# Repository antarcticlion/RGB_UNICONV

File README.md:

# RGB_UNICONV  

PCBs for Retro computer display connector convertion.  

---
  
## available configulations  
- Digital RGB DIN8p PC-8001 type pinout to DE15 VGA pinout (support ex. PC-8001/8801/9801/FM-7/MZ-700/Basic master level3/Pasopia PA7010/X1 turbo model 40)  
- Analog RGB DSUB15p 2row(DA15) PC-8801mk2SR type pinout to DE15 VGA pinout (support ex. PC-8801SR～/9801U･VM～/X68000)  
- Digital RGB DIN6p X1/X1turbo(without model 40) type pinout to DE15 VGA pinout  
- Analog RGB DSUB9p (DE9) PC-98XA/XL/XL2/RL type pinout to DE15 VGA pinout
- Digital RGB DSUB9p (DE9) FM77 type pinout to DE15 VGA pinout  (support FM77-D1/D2/L4/L2/AV)

---  
  
## news  

2022/09/27 Added PC98 Hi-resolution model (XA/XL/XL2/RL) DE9 configulation  
2022/09/27 Added FM77 Digital RGB 8 colors (D1/D2/L2/L4(8color only)/AV) DE9 configulation  

2022/07/30 Each PCB: Added "Licensed under CERN-OHL-W v2" somewhere on the silkscreen.

2022/07/20 Added X1/X1turbo DIN6 configulation  
2022/07/20 Added PC8801SR etc. DA15 configulation  
  
2022/07/09 Added pin type DE15 out PCB  
  
2022/06/25 Added the assembly procedure to the wiki. Since it is written in Japanese, please machine-translate it into your native language.  
https://github.com/antarcticlion/RGB_UNICONV/wiki/How-to-make  

---
## photos  

---

## GERBERs and BOMs

---  

### Digital RGB DIN8p PC-8001 type pinout to DE15 VGA pinout (support ex. PC-8001/8801/9801/FM-7/MZ-700/Pasopia PA7010/Basic master level3/X1 turbo model 40)  
  Received a report on the operation of the PC6001Mk2 (8 colors), and SMC777 (digital RGB).  
  
  #### lastest gerber 
  ##### DIN8_PC8001_IN PCB  
　　　https://github.com/antarcticlion/RGB_UNICONV/raw/main/DIN8_PC8001_IN/gerber/RGB_CONN_CHG_DIN8_ST4A.zip  
　　　PC-8001 type pin-out RGB display 8-pin DIN connector Breakout board.  
　　　Adjust the level using a 150Ω resistor.  

  ##### ANGLE_CHANGE_MID PCB 
　　　https://github.com/antarcticlion/RGB_UNICONV/blob/main/ANGLE_CHANGE_MID/gerber/RGB_CONN_CHG_MID_ST3A.zip  
　　　By sandwiching this board between the input board and the output board, the position of the signal pin is changed by 90 degrees.  
　　　Used when the connector interferes.  
　　　You can also combine two boards to extend the overall length.  
　　　When using two board for extension, make sure that the direction and orientation are the same.  
　　　Doing so will cause the signal to return to its original position.  

  ##### DE15_OUT PCB  
　　　https://github.com/antarcticlion/RGB_UNICONV/raw/main/DE15_OUT/gerber/RGB_CONN_CHG_DE15_CUP_ST2A.zip  
　　　Breakout board for solder cup type D-sub 15-pin 3-rows (DE15) connector.  
  
　　　https://github.com/antarcticlion/RGB_UNICONV/raw/main/DE15_OUT/gerber/RGB_CONN_CHG_DE15_ST1A.zip  
　　　Breakout board for pin type D-sub 15-pin 3-rows (DE15) connector.  

#### BOM (short profile)  
 - DIN8_PC8001_IN PCB x1  
 - DE15_OUT PCB x1  
 - 150ohm register x3  
 - DE15 female connector (solder cup) x1  
 - PCB mount din8 connector x1  
 - long pin header(minimum height 6mm) 3p x2  
  
#### BOM (90° angle profile)  
 - DIN8_PC8001_IN PCB x1  
 - ANGLE_CHANGE_MID PCB x1  
 - DE15_OUT PCB x1  
 - 150ohm register x3  
 - DE15 female connector (solder cup) x1  
 - PCB mount din8 connector x1  
 - long pin header(minimum height 6mm) 3p x4  
  
#### BOM (long profile)  
 - DIN8_PC8001_IN PCB x1  
 - ANGLE_CHANGE_MID PCB x2  
 - DE15_OUT PCB x1  
 - 150ohm register x3  
 - DE15 female connector (solder cup) x1  
 - PCB mount din8 connector x1  
 - long pin header(minimum height 6mm) 3p x6  

---  

### Analog RGB DSUB15p 2row(DA15) PC-8801mk2SR type pinout to DE15 VGA pinout (support ex. PC-8801SR～/9801U･VM～/X68000)  

#### lastest gerber 
##### DA15_PC88SR_IN PCB  
  https://github.com/antarcticlion/RGB_UNICONV/raw/main/DA15_88SR_IN/gerber/RGB_CONN_CHG_DA15_PC88SR_ST2A.zip  

PC-8801mk2SR type pin-out RGB display D-Sub 15pin 2row connector(Solder cup type) Breakout board.
CSYNC and Audio L R are pulled out in the optional pinout.
Confirmed that the CSYNC signal is output by 88SR generations.  and by XL, VX, DX, DA, FA on PC98. It has appeared in major models up to FA, but it seems that it has not appeared since then.
GS / 9821S is unknown.
It seems that PC286 / 386/486 is not available in later models. Probably not all models of X68000 are out.

Audio L R can be expected to output on all models of PC88SR or later / X68000. In PC98, it seems that it is output in the model equipped with FM sound source on the motherboard (confirmed with 98DA)  
On the YM2203-equipped machine, the same sound is produced for both LR.  

##### CSYNC_ANGLE_CHANGE_MID PCB  
https://github.com/antarcticlion/RGB_UNICONV/raw/main/ANGLE_CHANGE_MID/gerber/RGB_CONN_CHG_MID_ST3A.zip  

This angle-change-PCB have prepared a jumper so that you can select the relay of CSYNC and HSYNC that are pulled out as an option.  
This makes it possible to directly connect a PC-8801mk2SR, etc. to the GBS8200 / 8220 / HD-VC9900.  

#### BOM (short profile)  
 - DA15_PC88SR_IN PCB x1  
 - DE15_OUT PCB x1  
 - DA15 male connector (solder cup) x1  
 - DE15 female connector (solder cup) x1  
 - long pin header(minimum height 6mm) 3p x2  
  
#### BOM (90° angle profile)  
 - DA15_PC88SR_IN PCB x1  
 - ANGLE_CHANGE_MID PCB x1  
 - DE15_OUT PCB x1  
 - DA15 male connector (solder cup) x1  
 - DE15 female connector (solder cup) x1  
 - long pin header(minimum height 6mm) 3p x4  
  
#### BOM (long profile)  
 - DA15_PC88SR_IN PCB x1  
 - ANGLE_CHANGE_MID PCB x2  
 - DE15_OUT PCB x1  
 - DA15 male connector (solder cup) x1  
 - DE15 female connector (solder cup) x1  
 - long pin header(minimum height 6mm) 3p x6  

#### BOM (90° angle profile with csync)  
 - DA15_PC88SR_IN PCB x1  
 - CSYNC_ANGLE_CHANGE_MID PCB x1  
 - DE15_OUT PCB x1  
 - DA15 male connector (solder cup) x1  
 - DE15 female connector (solder cup) x1  
 - long pin header(minimum height 6mm) 3p x3  
 - long pin header(minimum height 6mm) 4p x1  
  
#### BOM (long profile with csync)  
 - DA15_PC88SR_IN PCB x1  
 - CSYNC_ANGLE_CHANGE_MID PCB x1  
 - ANGLE_CHANGE_MID PCB x1  
 - DE15_OUT PCB x1  
 - DA15 male connector (solder cup) x1  
 - DE15 female connector (solder cup) x1  
 - long pin header(minimum height 6mm) 3p x5  
 - long pin header(minimum height 6mm) 4p x1  

---

### Digital RGB DIN6p X1/X1turbo(without model 40) type pinout to DE15 VGA pinout  
  
  #### lastest gerber 
  ##### DIN6_X1_IN PCB  
　　　https://github.com/antarcticlion/RGB_UNICONV/raw/main/DIN6_X1_IN/gerber/RGB_CONN_CHG_DIN6_ST4A.zip  
　　　X1/X1turbo type pin-out RGB display 6-pin DIN connector Breakout board.  
　　　Adjust the level using a 150Ω resistor.  

#### BOM (short profile)  
 - DIN6_X1_IN PCB x1  
 - DE15_OUT PCB x1  
 - 150ohm register x3  
 - DE15 female connector (solder cup) x1  
 - PCB mount din8 connector x1  
 - long pin header(minimum height 6mm) 3p x2  
  
#### BOM (90° angle profile)  
 - DIN6_X1_IN PCB x1  
 - ANGLE_CHANGE_MID PCB x1  
 - DE15_OUT PCB x1  
 - 150ohm register x3  
 - DE15 female connector (solder cup) x1  
 - PCB mount din8 connector x1  
 - long pin header(minimum height 6mm) 3p x4  
  
#### BOM (long profile)  
 - DIN6_X1_IN PCB x1  
 - ANGLE_CHANGE_MID PCB x2  
 - DE15_OUT PCB x1  
 - 150ohm register x3  
 - DE15 female connector (solder cup) x1  
 - PCB mount din8 connector x1  
 - long pin header(minimum height 6mm) 3p x6  

---

### Analog RGB DSUB9p (DE9) PC-98XA/XL/XL2/RL type pinout to DE15 VGA pinout  
  
  #### lastest gerber  
  ##### DE9_PC98XL_IN PCB  
　　　https://github.com/antarcticlion/RGB_UNICONV/raw/main/DE9_PC98XL_IN/gerber/RGB_CONN_CHG_DE9_98XL_ST2A.zip  
　　　PC-98XA/XL/XL2/RL type pinout RGB display DSUB 9p (DE9) connector Breakout board.  

#### BOM (short profile)  
 - DE9_PC98XL_IN PCB x1  
 - DE15_OUT PCB x1  
 - DE15 female connector (solder cup) x1  
 - DE9 male connector (solder cup) x1  
 - long pin header(minimum height 6mm) 3p x2  
  
#### BOM (90° angle profile)  
 - DE9_PC98XL_IN PCB x1  
 - ANGLE_CHANGE_MID PCB x1  
 - DE15_OUT PCB x1  
 - DE15 female connector (solder cup) x1  
 - DE9 male connector (solder cup) x1  
 - long pin header(minimum height 6mm) 3p x4  
  
#### BOM (long profile)  
 - DE9_PC98XL_IN PCB x1  
 - ANGLE_CHANGE_MID PCB x2  
 - DE15_OUT PCB x1  
 - DE15 female connector (solder cup) x1  
 - DE9 male connector (solder cup) x1  
 - long pin header(minimum height 6mm) 3p x6  

---

### Digital RGB DSUB9p (DE9) FM77 type pinout to DE15 VGA pinout  (support FM77-D1/D2/L4/L2/AV)
  
  #### lastest gerber 
  ##### DE9_FM77_IN PCB  
　　　https://github.com/antarcticlion/RGB_UNICONV/raw/main/DE9_FM77_IN/gerber/RGB_CONN_CHG_DE9_FM77_ST2A.zip  
　　　FM77 type pinout RGB display DSUB 9p (DE9) connector Breakout board.  
　　　Adjust the level using a 150Ω resistor.  

  ##### ANGLE_CHANGE_DIGITAL_MID PCB
　　　https://github.com/antarcticlion/RGB_UNICONV/raw/main/ANGLE_CHANGE_DIGITAL_MID/gerber/RGB_CONN_CHG_MID_DIGITAL_ST1A.zip  
　　　Digital RGB signal level control angle change board  

#### BOM (short profile)  
  N/A  
  
#### BOM (90° angle profile)  
 - DE9_FM77_IN PCB x1  
 - ANGLE_CHANGE_DIGITAL_MID PCB x1  
 - DE15_OUT PCB x1  
 - 150ohm register x3  
 - DE15 female connector (solder cup) x1  
 - DE9 male connector (solder cup) x1  
 - long pin header(minimum height 6mm) 3p x4  
  
#### BOM (long profile)  
 - DE9_FM77_IN PCB x1  
 - ANGLE_CHANGE_DIGITAL_MID PCB x2  
 - ANGLE_CHANGE_MID PCB x1  
 - DE15_OUT PCB x1  
 - 150ohm register x3  
 - DE15 female connector (solder cup) x1  
 - DE9 male connector (solder cup) x1  
 - long pin header(minimum height 6mm) 3p x6  

---
#  Source of reference
 - PC-8001 type DIN8 RGB Display connector pinout : 改訂2版 PC-9800シリーズ テクニカルデータブック HARDWAER編 ISBN4-7561-1008-8
 - VGA DE15 RGB Display connector pinout : SECOND EDITION THE PROGRAMMER'S PC SOURCEBOOK ISBN1-55615-321-X
 - X1センター -> インターフェイスコネクタ : http://www.x1center.org/
 - Retro PC Gallery (by はせりん) -> 番外編７：FM-8/7/77/77AVシリーズの微妙な非互換性 : http://haserin09.la.coocan.jp/
---

# LICENSE

Copyright Antarcticlion 2022.
This source describes Open Hardware and is licensed under the CERN-OHLW v2

You may redistribute and modify this documentation and make products using it under the terms of the CERN-OHL-W v2 (https:/cern.ch/cern-ohl).
This documentation is distributed WITHOUT ANY EXPRESS OR IMPLIED WARRANTY, INCLUDING OF MERCHANTABILITY, SATISFACTORY QUALITY AND FITNESS FOR A PARTICULAR PURPOSE. Please see the CERN-OHL-W v2 for applicable conditions.
Source location: https://github.com/antarcticlion/RGB_UNICONV
As per CERN-OHL-W v2 section 4.1, should You produce hardware based on these sources, You must maintain the Source Location visible on the external case of the White Rabbit switch or other product you make using this documentation.

 CERN Open Hardware Licence Version 2 - Weakly Reciprocal
- https://spdx.org/licenses/CERN-OHL-W-2.0.html  
- https://github.com/antarcticlion/RGB_UNICONV/raw/main/cern_ohl_w_v2.pdf PDF  
- https://github.com/antarcticlion/RGB_UNICONV/raw/main/cern_ohl_w_v2_howto.pdf PDF

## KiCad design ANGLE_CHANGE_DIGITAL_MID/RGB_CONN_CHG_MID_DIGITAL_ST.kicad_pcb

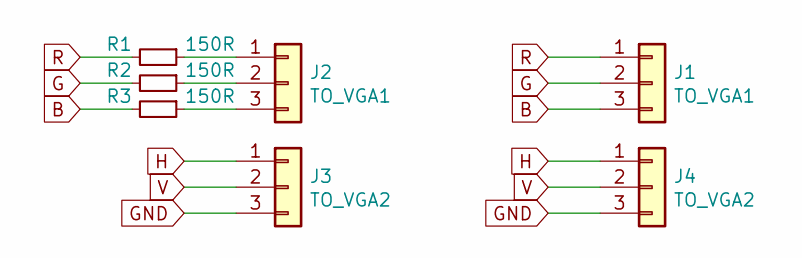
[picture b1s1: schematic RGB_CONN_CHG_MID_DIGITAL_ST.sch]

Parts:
J1, J2: TO_VGA1; PinHeader_1x03_P2.54mm_Vertical
J3, J4: TO_VGA2; PinHeader_1x03_P2.54mm_Vertical
R1, R2, R3: 150R; R_Axial_DIN0204_L3.6mm_D1.6mm_P5.08mm_Horizontal

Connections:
B: J1.3, R3.2
G: J1.2, R2.2
GND: J3.3, J4.3
H: J3.1, J4.1
unnamed: J2.1, R1.1
unnamed: J2.2, R2.1
unnamed: J2.3, R3.1
R: J1.1, R1.2
V: J3.2, J4.2

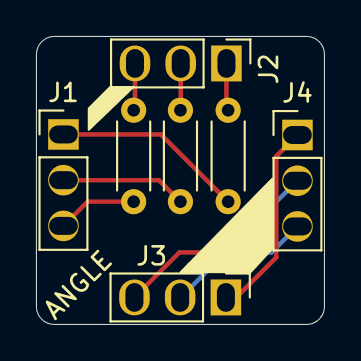
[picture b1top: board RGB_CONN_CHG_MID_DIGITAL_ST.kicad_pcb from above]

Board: 2 copper layers, 16.0 x 16.0 mm, 7 parts (0 on the bottom side), 9 nets.

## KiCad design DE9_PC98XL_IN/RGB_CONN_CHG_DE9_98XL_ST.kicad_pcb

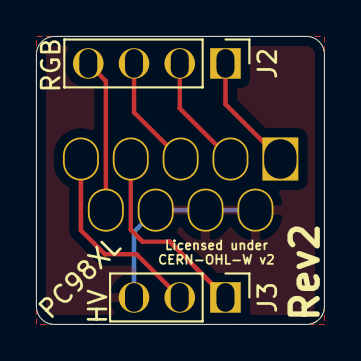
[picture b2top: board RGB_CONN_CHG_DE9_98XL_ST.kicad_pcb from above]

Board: 2 copper layers, 16.0 x 16.0 mm, 3 parts (1 on the bottom side), 7 nets.

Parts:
J1: PC98XL; DSUB-9_Male_Vertical_P2.77x2.84mm
J2: RGB; PinHeader_1x04_P2.54mm_Vertical
J3: HV; PinHeader_1x03_P2.54mm_Vertical

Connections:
B: J1.3, J2.3
G: J1.2, J2.2
GND: J1.6, J1.7, J1.8, J3.3
H: J1.4, J3.1
R: J1.1, J2.1
SENSE: J1.9, J2.4
V: J1.5, J3.2

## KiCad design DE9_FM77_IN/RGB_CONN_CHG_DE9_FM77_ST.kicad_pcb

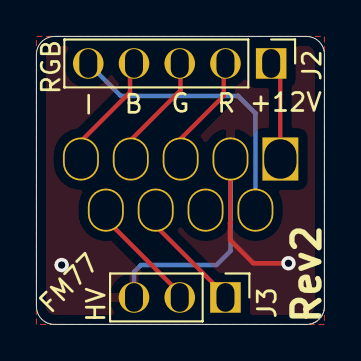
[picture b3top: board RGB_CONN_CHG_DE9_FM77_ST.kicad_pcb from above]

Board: 2 copper layers, 16.0 x 16.0 mm, 3 parts (1 on the bottom side), 8 nets.

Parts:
J1: FM77; DSUB-9_Male_Vertical_P2.77x2.84mm
J2: RGB; PinHeader_1x05_P2.54mm_Vertical
J3: HV; PinHeader_1x03_P2.54mm_Vertical

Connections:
+12V: J1.1, J2.1
B: J1.5, J2.4
G: J1.4, J2.3
GND: J1.2, J3.3
H: J1.8, J3.1
I: J1.6, J2.5
R: J1.3, J2.2
V: J1.9, J3.2

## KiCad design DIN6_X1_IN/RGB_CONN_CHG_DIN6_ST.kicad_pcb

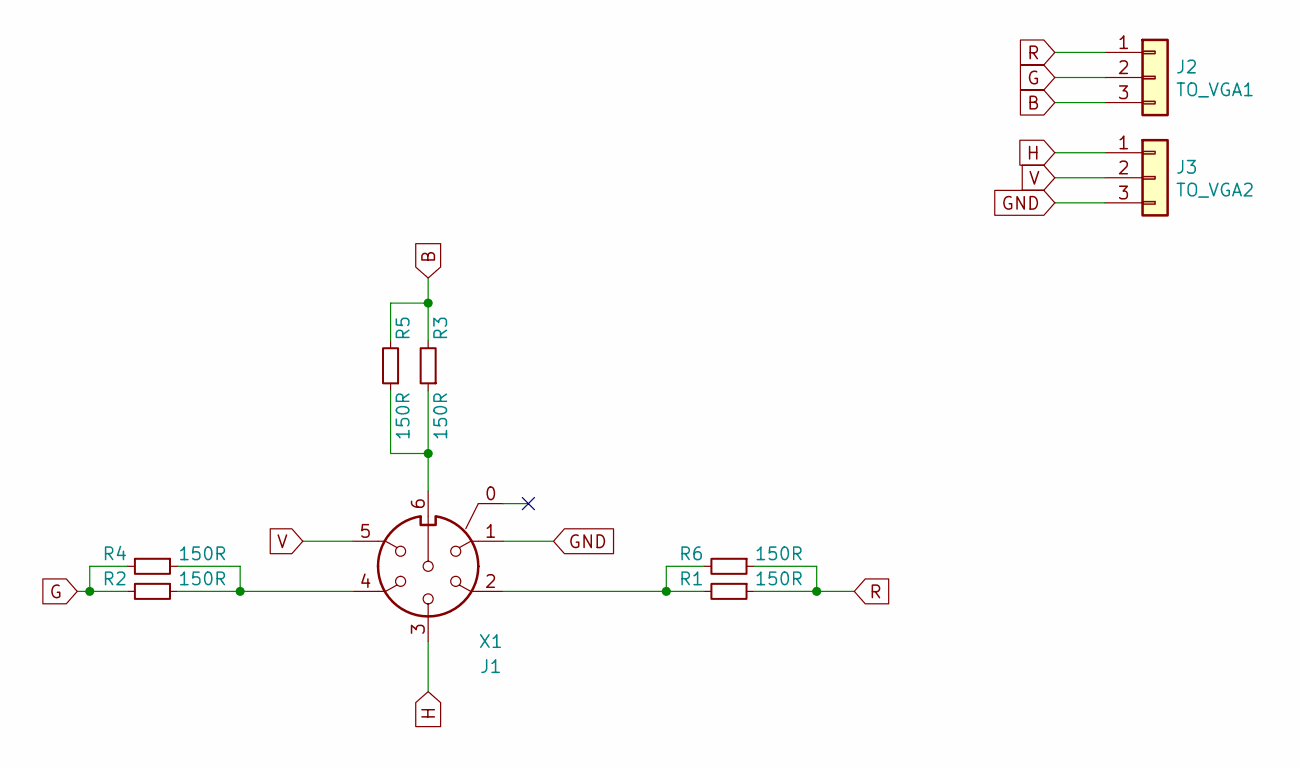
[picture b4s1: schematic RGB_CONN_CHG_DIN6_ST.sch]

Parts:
J1: X1; DIN6_PLG_PCB
J2: TO_VGA1; PinHeader_1x03_P2.54mm_Vertical
J3: TO_VGA2; PinHeader_1x03_P2.54mm_Vertical
R1, R2, R3: 150R; R_Axial_DIN0204_L3.6mm_D1.6mm_P5.08mm_Horizontal
R4, R5, R6: 150R; R_0603_1608Metric_Pad1.05x0.95mm_HandSolder

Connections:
B: J2.3, R3.2, R5.2
G: J2.2, R2.2, R4.2
GND: J1.1, J3.3
H: J1.3, J3.1
unnamed: J1.2, R1.2, R6.2
unnamed: J1.4, R2.1, R4.1
unnamed: J1.6, R3.1, R5.1
R: J2.1, R1.1, R6.1
V: J1.5, J3.2

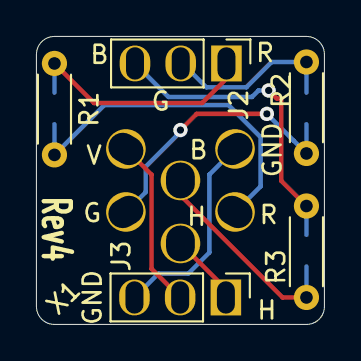
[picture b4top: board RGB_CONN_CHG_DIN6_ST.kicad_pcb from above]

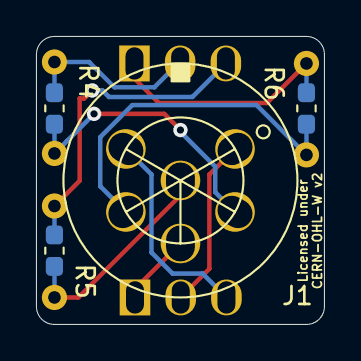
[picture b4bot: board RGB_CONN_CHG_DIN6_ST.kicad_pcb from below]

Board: 2 copper layers, 16.0 x 16.0 mm, 9 parts (4 on the bottom side), 9 nets.

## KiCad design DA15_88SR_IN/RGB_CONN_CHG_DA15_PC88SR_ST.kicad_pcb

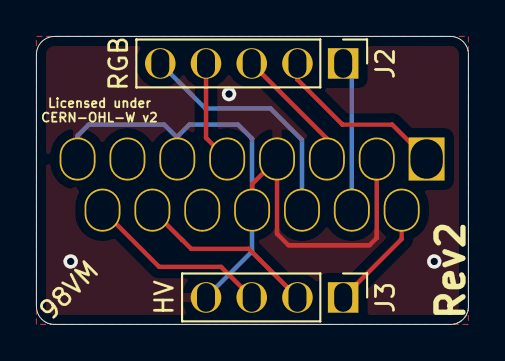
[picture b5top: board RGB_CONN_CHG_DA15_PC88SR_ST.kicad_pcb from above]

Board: 2 copper layers, 24.0 x 16.0 mm, 3 parts (1 on the bottom side), 9 nets.

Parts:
J1: 98VM; DSUB-15_Male_Vertical_P2.77x2.84mm
J2: RGB; PinHeader_1x05_P2.54mm_Vertical
J3: HV; PinHeader_1x04_P2.54mm_Vertical

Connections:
AUDIO_L: J1.10, J2.1
AUDIO_R: J1.11, J2.5
B: J1.5, J2.4
CSYNC: J1.9, J3.1
G: J1.3, J2.3
GND: J1.2, J1.4, J1.6, J1.8, J1.12, J3.4
H: J1.14, J3.2
R: J1.1, J2.2
V: J1.15, J3.3

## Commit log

2022-06-14 ライセンスのPDFファイルが壊れていたので再アップロード
2022-07-23 LICENSE
2022-07-30 update f_silk
    added "Licensed under CERN-OHL-W v2"
2022-07-30 update silkscreen
    2022/07/30 Each PCB: Added "Licensed under CERN-OHL-W v2" somewhere on the silkscreen.
2022-09-27 Add FM77 / Hi-reso 98
